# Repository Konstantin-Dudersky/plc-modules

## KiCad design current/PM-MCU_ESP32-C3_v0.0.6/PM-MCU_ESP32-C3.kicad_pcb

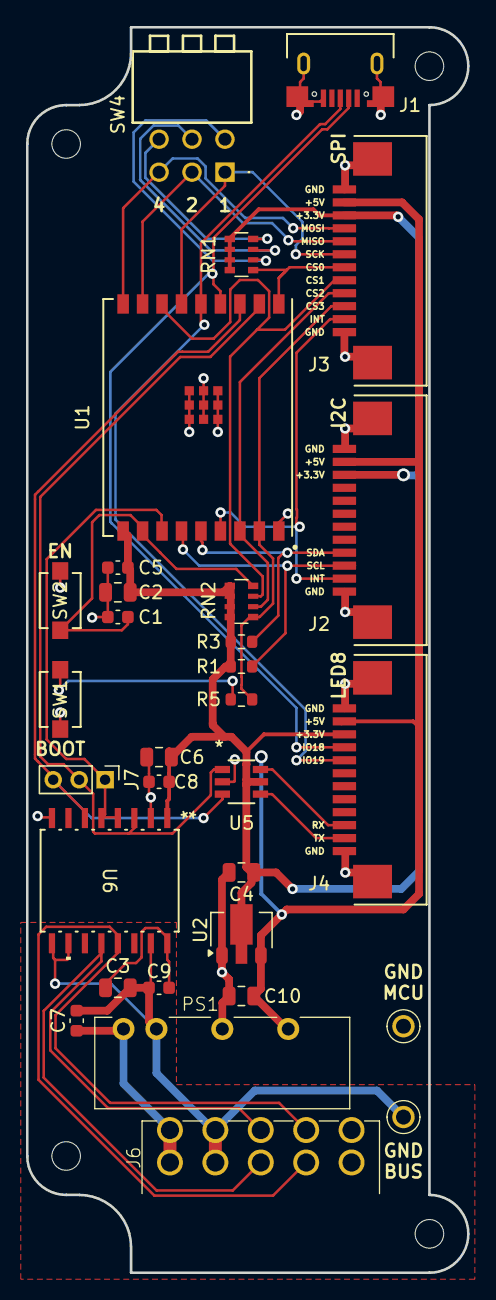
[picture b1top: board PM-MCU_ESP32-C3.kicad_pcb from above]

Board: 2 copper layers, 34.0 x 96.0 mm, 35 parts (0 on the bottom side), 31 nets.

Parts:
C1, C5, C7: 1uF; C_0603_1608Metric
C2, C3, C6, C10: 10uF; C_0805_2012Metric
C4: 22uF; C_0805_2012Metric
C8, C9: 100nF; C_0603_1608Metric
H1, H2, H3, H4: MountingHole_M2
J1: U254-051T-4BH83-S1S; CONN5_H83-S1S_XKB
J2, J3, J4: AFA07-S12FCC-00; CONN10_AFA07-S12_JUS
J6: 15EDGRHC-THR-3.5-10P
J7: PinHeader_01x03_P2.00_THT_straight; PinHeader_1x03_P2.00mm_Vertical
PS1: 24V/5V; B2405LS-1WR3
R1, R3: 3k3; R_0603_1608Metric
R5: 330R; R_0603_1608Metric
RN1, RN2: 10k; R_Array_Convex_4x0603
SW1, SW2: Button; SW_TS-1088_XNP-M
SW4: DIP 3 pos; DA03BLP
U1: ESP32-C3-WROOM-02U-N4; ESP32-C3-WROOM-02U_EXP
U2: CJA1117B-3.3; SOT-89-3
U3, U4: 5117
U5: SN74LVC2G14DBVR; DBV6-M
U6: CA-IS3098W; SOIC16-WBW_CLG

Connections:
+3.3V_BUS: C3.1, C9.1, U6.16 (VISO)
+3.3V_MCU: C2.1, C4.1, C5.1, C6.1, C8.1, J2.10, J3.10, J4.10, R1.1, R3.1, RN1.1 (R1.1), RN1.2 (R2.1), RN1.3 (R3.1), RN1.4 (R4.1), RN2.1 (R1.1), RN2.2 (R2.1), RN2.3 (R3.1), RN2.4 (R4.1), U1.1 (3V3), U2.2 (OUTPUT), U5.5 (VCC), U6.1 (VDD)
+5V_MCU: C10.1, J2.11, J3.11, J4.11, PS1.6 (+V), U2.3 (INPUT)
+24V_BUS: C7.1, J6.1, J6.6 (Pin_2), PS1.1 (Vin)
/A: J6.3, J6.8 (Pin_6), U6.12 (A)
/B: J6.4, J6.9 (Pin_8), U6.13 (B)
/CS0: J3.6, RN1.5 (R4.2), U1.10 (IO10)
/CS1: J3.5, RN2.7 (R2.2), U1.16 (IO2)
/CS2: J3.4, RN2.6 (R3.2), U1.7 (IO8)
/CS3: J3.3, R5.2, RN2.5 (R4.2), U1.8 (IO9)
/EN: C1.1, RN2.8 (R1.2), SW2.2, U1.2 (EN)
/INT: J2.2, J3.2, U1.6 (IO7)
/MISO: J3.8, SW4.2, U1.17 (IO1)
/MOSI: J3.9, SW4.3, U1.18 (IO0)
/SCK: J3.7, SW4.1, U1.15 (IO3)
/SCL: J2.3, R1.2, U1.4 (IO5)
/SDA: J2.4, R3.2, U1.5 (IO6)
/UART_RTS: J7.1, U1.3 (IO4), U6.4 (RE), U6.5 (DE)
/UART_RX: J7.2, U1.11 (RXD_(IO20)), U5.1 (1A), U6.3 (RO)
/UART_TX: J7.3, U1.12 (TXD_(IO21)), U5.3 (2A), U6.6 (DI)
/USB_D+: J1.3 (D+), J4.8, U1.14 (IO19_(USB_D+))
/USB_D-: J1.2 (D-), J4.9, U1.13 (IO18_(USB_D-))
GND_BUS: C3.2, C7.2, C9.2, J6.2 (Pin_3), J6.7 (Pin_4), PS1.2 (GND), U4.1, U6.9 (GNDB), U6.10 (SEL), U6.15 (GNDB)
GND_MCU: C1.2, C2.2, C4.2, C5.2, C6.2, C8.2, C10.2, J1.5 (GND), J2.1, J2.12 (Pin_11), J2.13 (Pin_11), J3.1, J3.12 (Pin_11), J3.13 (Pin_11), J4.1, J4.12 (Pin_11), J4.13 (Pin_11), PS1.4 (0V), SW1.1, SW2.1, U1.9 (GND), U1.EPAD, U2.1 (GND), U3.1, U5.2 (GND), U6.2 (GNDA), U6.8 (GNDA)
unnamed: J4.2, U5.4 (2Y)
unnamed: J4.3, U5.6 (1Y)
unnamed: R5.1, SW1.2
unnamed: RN1.8 (R1.2), SW4.4
unnamed: RN1.7 (R2.2), SW4.5
unnamed: RN1.6 (R3.2), SW4.6
PE: J6.5 (Pin_9), J6.10

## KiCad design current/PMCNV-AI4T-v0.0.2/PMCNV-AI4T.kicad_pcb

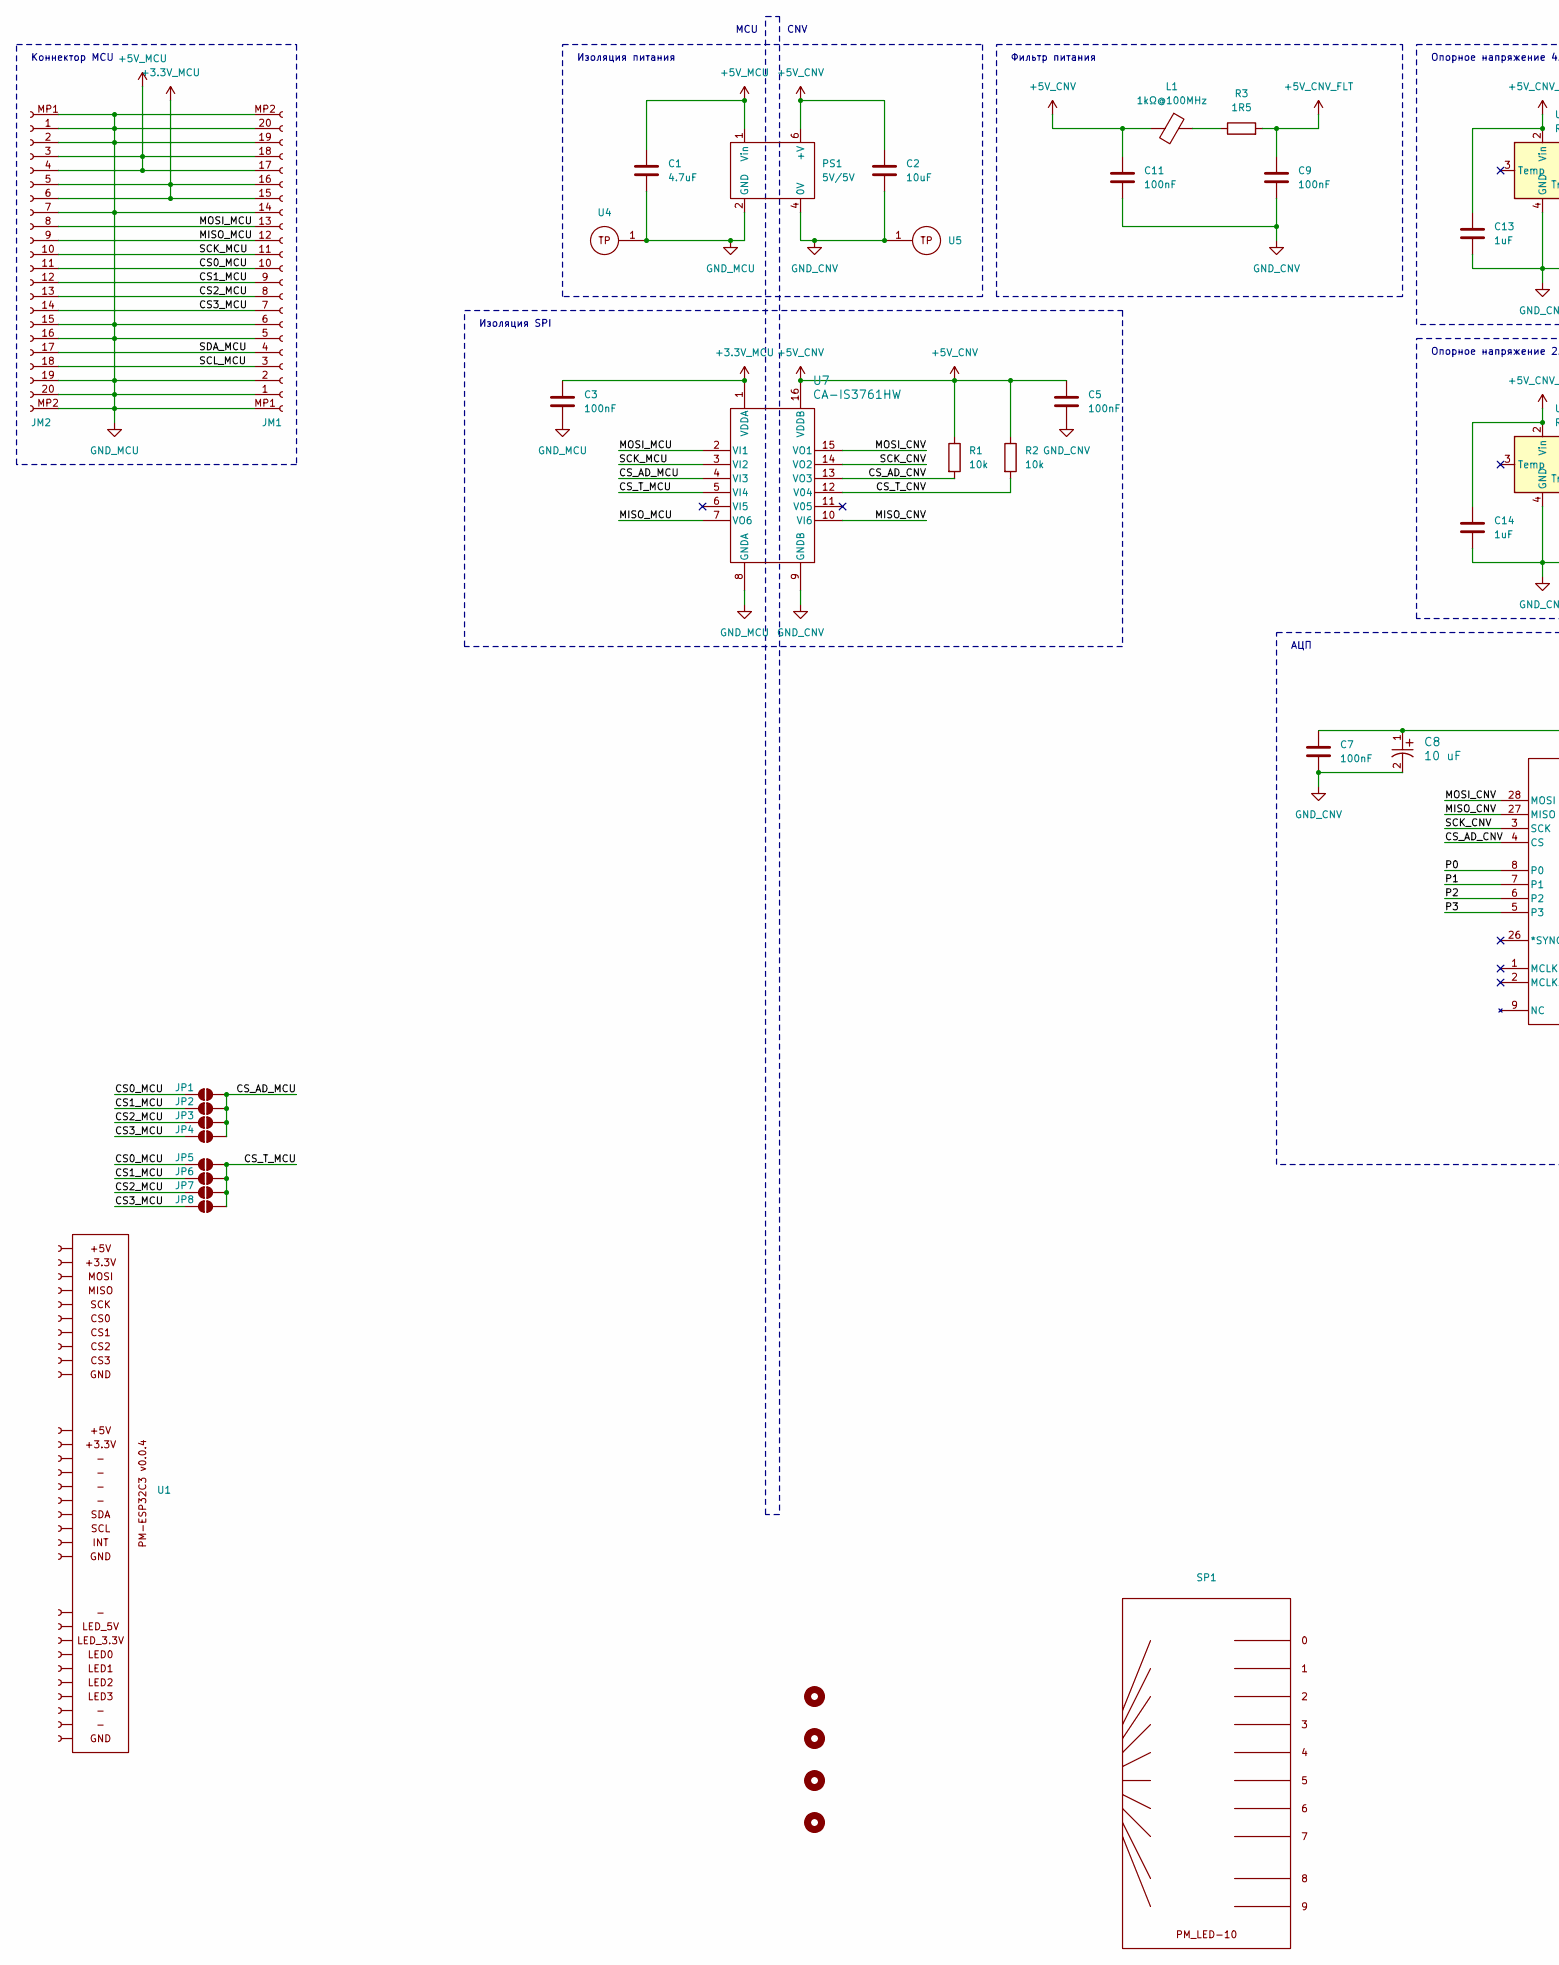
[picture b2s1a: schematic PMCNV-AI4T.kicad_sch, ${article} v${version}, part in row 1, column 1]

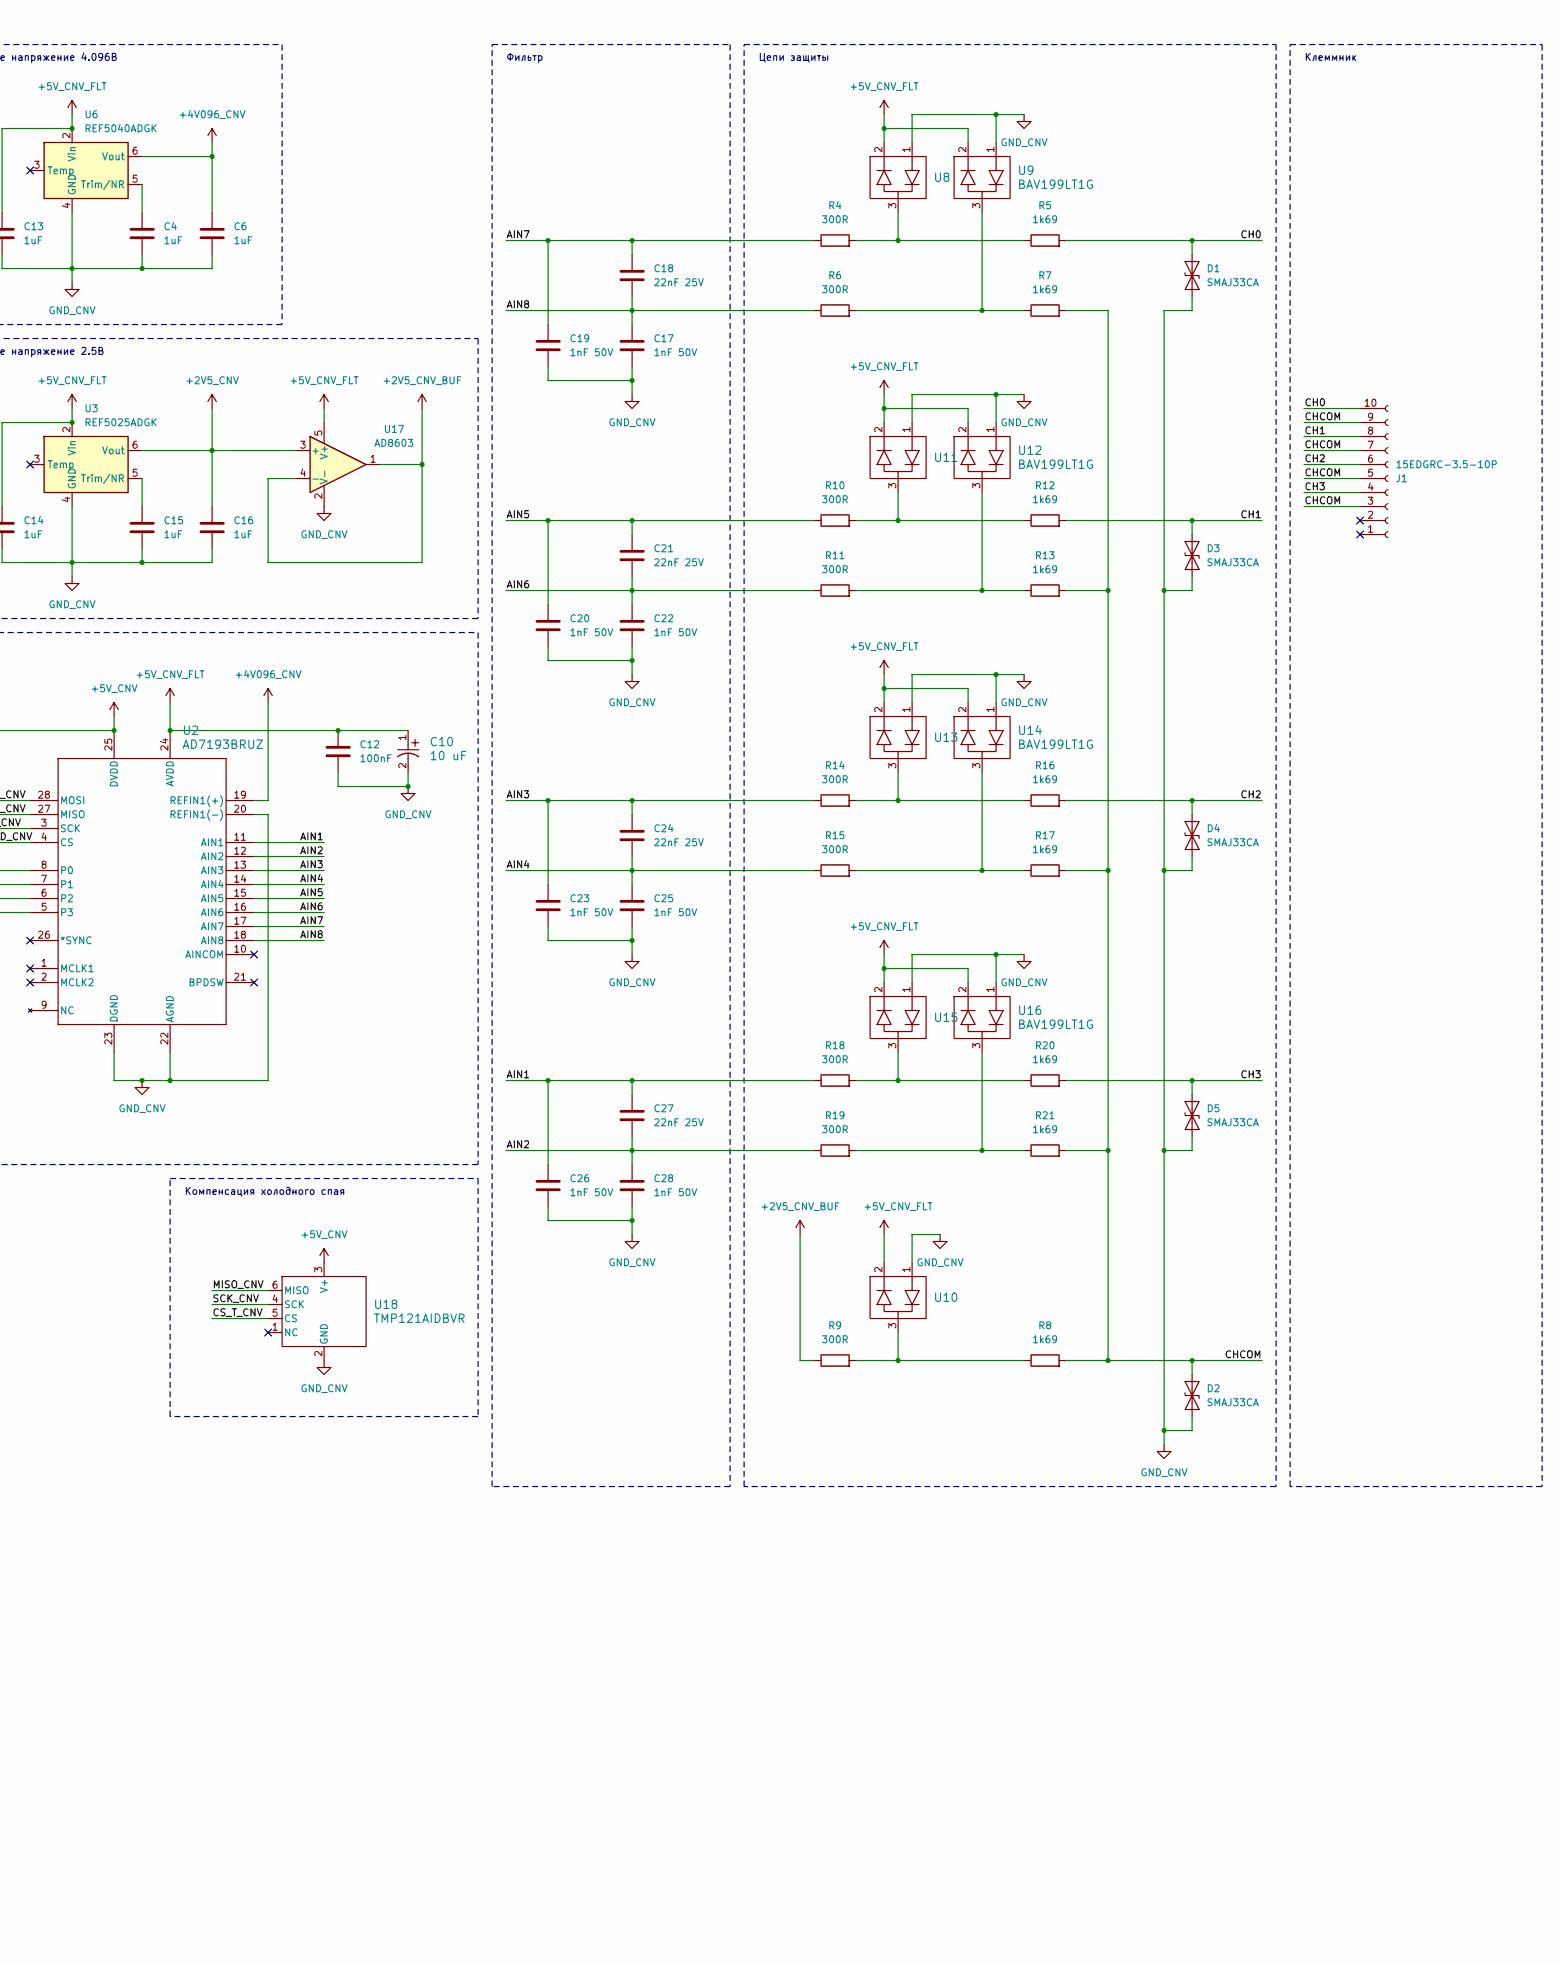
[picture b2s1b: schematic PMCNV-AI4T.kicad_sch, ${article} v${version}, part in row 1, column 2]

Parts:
C1: 4.7uF; C_0805_2012Metric; part_ipn C_4.7uF_16V_0805_MLCC-X7R
C2: 10uF; C_0805_2012Metric; part_ipn C_10uF_16V_0805_MLCC-X7R
C3, C5, C7, C9, C11, C12: 100nF; C_0603_1608Metric; part_ipn C_100nF_16V_0603_MLCC-X7R
C4, C6, C13, C14, C15, C16: 1uF; C_0603_1608Metric; part_ipn C_1uF_16V_0603_MLCC-X7R
C8, C10: 10 uF; TAJA_AVX-M; part_ipn TAJA106M016RNJ
C17, C19, C20, C22, C23, C25, C26, C28: 1nF 50V; C_0603_1608Metric; part_ipn C_1nF_50V_0603_MLCC-X7R
C18, C21, C24, C27: 22nF 25V; C_0603_1608Metric; part_ipn C_22nF_25V_0603_MLCC-X7R
D1, D2, D3, D4, D5: SMAJ33CA; SMASeries_LTF-M; part_ipn SMAJ33CA
H4, H5, H6, H7: MountingHole_M3
J1: 15EDGRC-3.5-10P; part_ipn 15EDGRC-3.5-10P
JM1, JM2: AFA07-S20FCC-00; AFA07S20FCA00; part_ipn AFA07-S20FCC-00
JP1, JP2, JP3, JP4, JP5, JP6, JP7, JP8: SolderJumper_2_Open; SolderJumper-2_P1.3mm_Open_RoundedPad1.0x1.5mm
L1: 1kΩ@100MHz; L_1206_3216Metric_Pad1.42x1.75mm_HandSolder; part_ipn FB_300mΩ_1kΩ@100MHz_1206
PS1: 5V/5V; B2405LS-1WR3; part_ipn B0505LS-1W
R1, R2: 10k; R_0603_1608Metric; part_ipn R_10k_0603_1%
R3: 1R5; R_0603_1608Metric; part_ipn R_1R5_0603_1%
R4, R6, R9, R10, R11, R14, R15, R18, R19: 300R; R_0603_1608Metric; part_ipn R_300R_0603_1%
R5, R7, R8, R12, R13, R16, R17, R20, R21: 1k69; R_0603_1608Metric; part_ipn R_1k69_0603_1%
SP1: PM_LED-xx-v0.0.1; part_ipn PM_LED-10-v0.0.1
U1: PM-ESP32C3_v0.0.5; part_ipn PM-ESP32C3_v0.0.4
U2: AD7193BRUZ; RU_28_ADI; part_ipn AD7193BRUZ
U3: REF5025ADGK; MSOP-8_3x3mm_P0.65mm
U4, U5: 5117; part_ipn Keystone_5117
U6: REF5040ADGK; MSOP-8_3x3mm_P0.65mm
U7: CA-IS3761HW; SOIC16-WBW_CLG-M; part_ipn CA-IS3761HW
U8, U9, U10, U11, U12, U13, U14, U15, U16: BAV199LT1G; SOT-23_ONS
U17: AD8603; TSOT-23-5
U18: TMP121AIDBVR; DBV6

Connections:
+2V5_CNV: C16.1, U3.6 (Vout), U17.3 (+)
+2V5_CNV_BUF: R9.1, U17.1, U17.4 (-)
+3.3V_MCU: C3.1, JM1.15 (Pin_11), JM1.16 (Pin_11), JM2.5, JM2.6, U7.1 (VDDA)
+4V096_CNV: C6.1, U2.19 (REFIN1(+)), U6.6 (Vout)
+5V_CNV: C2.1, C5.2, C7.1, C8.1, C11.1, L1.2, PS1.6 (+V), R1.1, R2.1, U2.25 (DVDD), U7.16 (VDDB), U18.3 (V+)
+5V_CNV_FLT: C9.1, C10.1, C12.1, C13.1, C14.1, R3.2, U2.24 (AVDD), U3.2 (Vin), U6.2 (Vin), U8.2, U9.2, U10.2, U11.2, U12.2, U13.2, U14.2, U15.2, U16.2, U17.5 (V+)
+5V_MCU: C1.1, JM1.17 (Pin_11), JM1.18 (Pin_11), JM2.3, JM2.4, PS1.1 (Vin)
/AIN1: C26.1, C27.1, R18.1, U2.11 (AIN1)
/AIN2: C27.2, C28.1, R19.1, U2.12 (AIN2)
/AIN3: C23.1, C24.1, R14.1, U2.13 (AIN3)
/AIN4: C24.2, C25.1, R15.1, U2.14 (AIN4)
/AIN5: C20.1, C21.1, R10.1, U2.15 (AIN5)
/AIN6: C21.2, C22.1, R11.1, U2.16 (AIN6)
/AIN7: C18.1, C19.1, R4.1, U2.17 (AIN7)
/AIN8: C17.1, C18.2, R6.1, U2.18 (AIN8)
/CH0: D1.2 (A2), J1.10, R5.2
/CH1: D3.2 (A2), J1.8, R12.2
/CH2: D4.2 (A2), J1.6, R16.2
/CH3: D5.2 (A2), J1.4, R20.2
/CHCOM: D2.2 (A2), J1.3, J1.5, J1.7, J1.9, R7.2, R8.2, R13.2, R17.2, R21.2
/CS0_MCU: JM1.10, JM2.11, JP1.1 (A), JP5.1 (A)
/CS1_MCU: JM1.9, JM2.12 (Pin_11), JP2.1 (A), JP6.1 (A)
/CS2_MCU: JM1.8, JM2.13 (Pin_11), JP3.1 (A), JP7.1 (A)
/CS3_MCU: JM1.7, JM2.14 (Pin_11), JP4.1 (A), JP8.1 (A)
/CS_AD_CNV: R1.2, U2.4 (CS), U7.13 (VO3)
/CS_AD_MCU: JP1.2 (B), JP2.2 (B), JP3.2 (B), JP4.2 (B), U7.4 (VI3)
/CS_T_CNV: R2.2, U7.12 (V04), U18.5 (CS)
/CS_T_MCU: JP5.2 (B), JP6.2 (B), JP7.2 (B), JP8.2 (B), U7.5 (VI4)
/MISO_CNV: U2.27 (MISO), U7.10 (VI6), U18.6 (MISO)
/MISO_MCU: JM1.12 (Pin_11), JM2.9, U7.7 (VO6)
/MOSI_CNV: U2.28 (MOSI), U7.15 (VO1)
/MOSI_MCU: JM1.13 (Pin_11), JM2.8, U7.2 (VI1)
/P0: U2.8 (P0)
/P1: U2.7 (P1)
/P2: U2.6 (P2)
/P3: U2.5 (P3)
/SCK_CNV: U2.3 (SCK), U7.14 (VO2), U18.4 (SCK)
/SCK_MCU: JM1.11, JM2.10, U7.3 (VI2)
/SCL_MCU: JM1.3, JM2.18 (Pin_11)
/SDA_MCU: JM1.4, JM2.17 (Pin_11)
GND_CNV: C2.2, C4.2, C5.1, C6.2, C7.2, C8.2, C9.2, C10.2, C11.2, C12.2, C13.2, C14.2, C15.2, C16.2, C17.2, C19.2, C20.2, C22.2, C23.2, C25.2, C26.2, C28.2, D1.1 (A1), D2.1 (A1), D3.1 (A1), D4.1 (A1), D5.1 (A1), PS1.4 (0V), U2.20 (REFIN1(-)), U2.22 (AGND), U2.23 (DGND), U3.4 (GND), U5.1, U6.4 (GND), U7.9 (GNDB), U8.1, U9.1, U10.1, U11.1, U12.1, U13.1, U14.1, U15.1, U16.1, U17.2 (V-), U18.2 (GND)
GND_MCU: C1.2, C3.2, JM1.1, JM1.2, JM1.5, JM1.6, JM1.14 (Pin_11), JM1.19 (Pin_11), JM1.20 (Pin_11), JM1.MP1 (Pin_11), JM1.MP2 (Pin_11), JM2.1, JM2.2, JM2.7, JM2.15 (Pin_11), JM2.16 (Pin_11), JM2.19 (Pin_11), JM2.20 (Pin_11), JM2.MP1 (Pin_11), JM2.MP2 (Pin_11), PS1.2 (GND), U4.1, U7.8 (GNDA)
unnamed: L1.1, R3.1
unnamed: R4.2, R5.1, U8.3
unnamed: R6.2, R7.1, U9.3
unnamed: R8.1, R9.2, U10.3
unnamed: R10.2, R12.1, U11.3
unnamed: R11.2, R13.1, U12.3
unnamed: R14.2, R16.1, U13.3
unnamed: R15.2, R17.1, U14.3
unnamed: R18.2, R20.1, U15.3
unnamed: R19.2, R21.1, U16.3
unnamed: C15.1, U3.5 (Trim/NR)
unnamed: C4.1, U6.5 (Trim/NR)

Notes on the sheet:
Опорное напряжение 2.5В
Опорное напряжение 4.096В
MCU
Изоляция питания
Изоляция SPI
Коннектор MCU
CNV
Фильтр питания
АЦП
Фильтр
Компенсация холодного спая
Цепи защиты
Клеммник

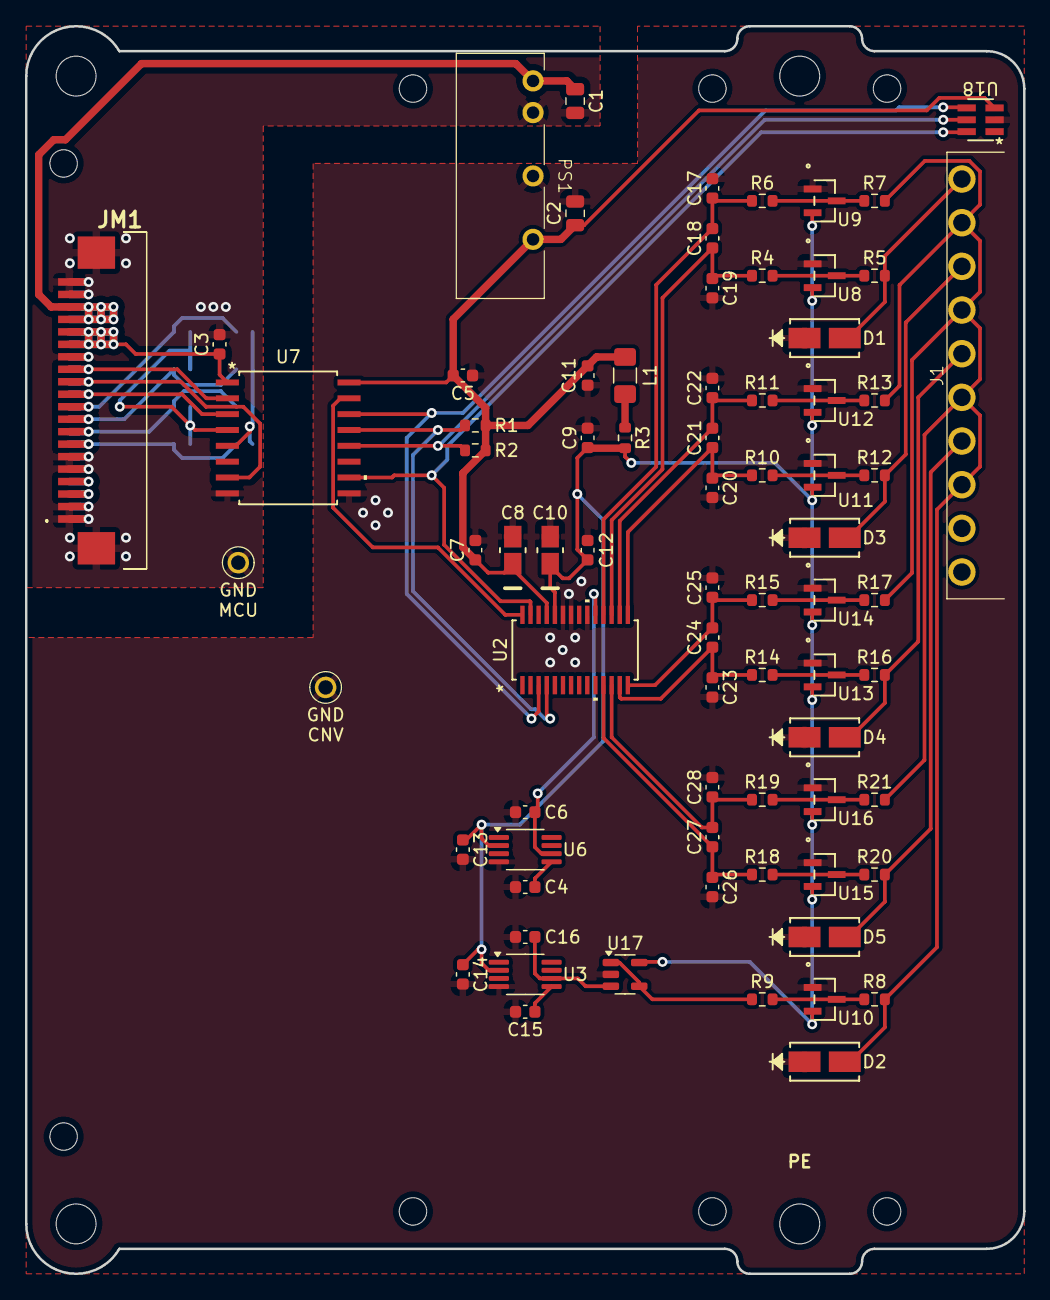
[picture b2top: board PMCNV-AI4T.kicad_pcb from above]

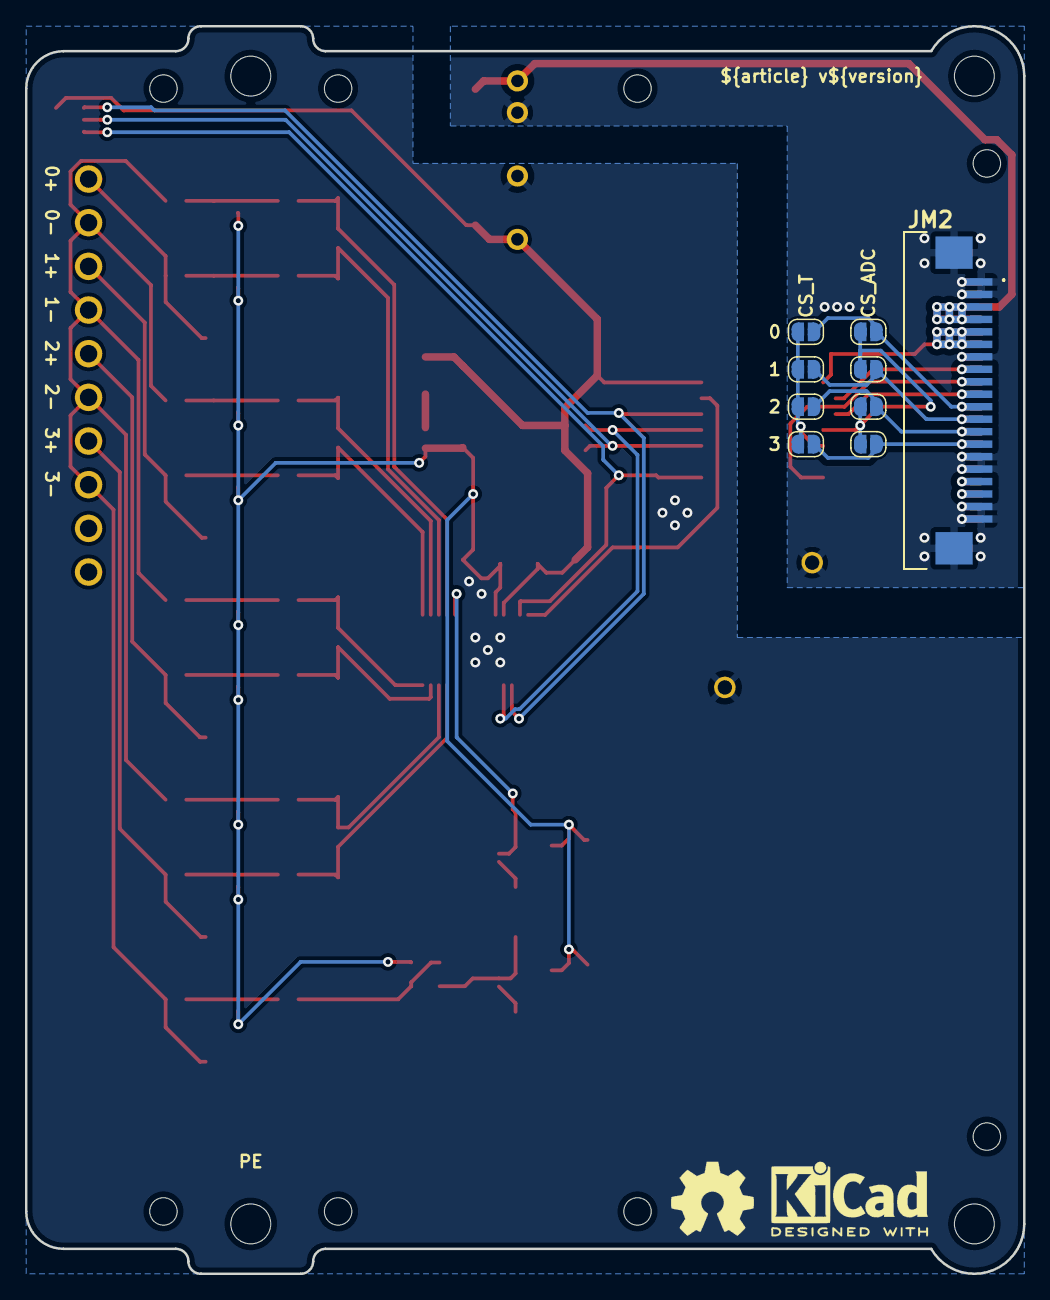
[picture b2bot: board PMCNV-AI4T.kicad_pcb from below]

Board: 2 copper layers, 80.0 x 100.0 mm, 92 parts (11 on the bottom side), 50 nets.

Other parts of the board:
kicad_logo: KiCad-Logo2_5mm_SilkScreen
oshw_logo: OSHW-Symbol_6.7x6mm_SilkScreen

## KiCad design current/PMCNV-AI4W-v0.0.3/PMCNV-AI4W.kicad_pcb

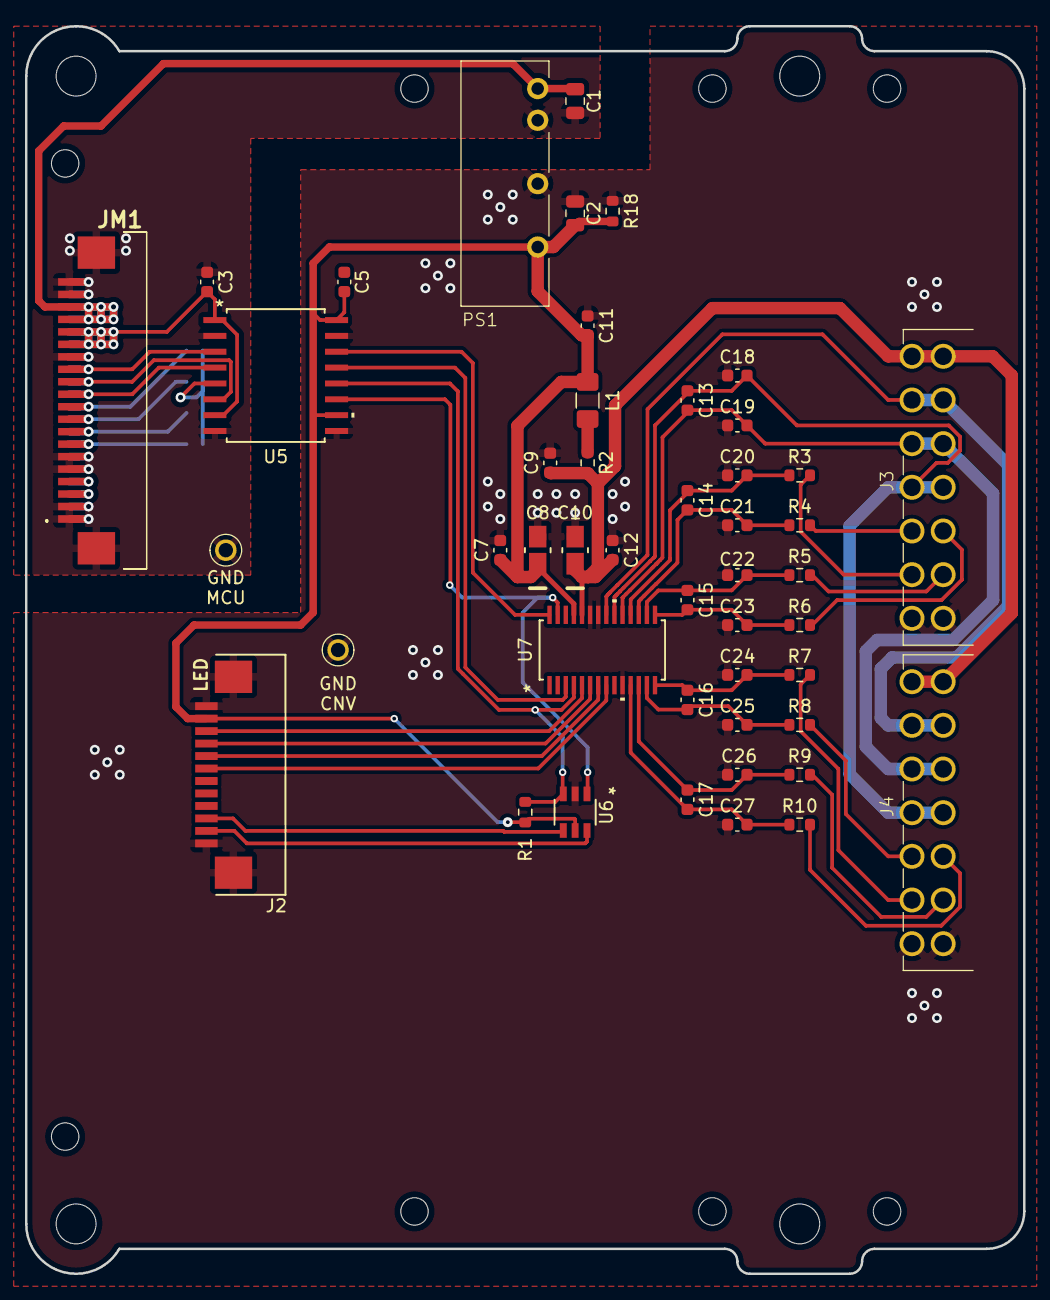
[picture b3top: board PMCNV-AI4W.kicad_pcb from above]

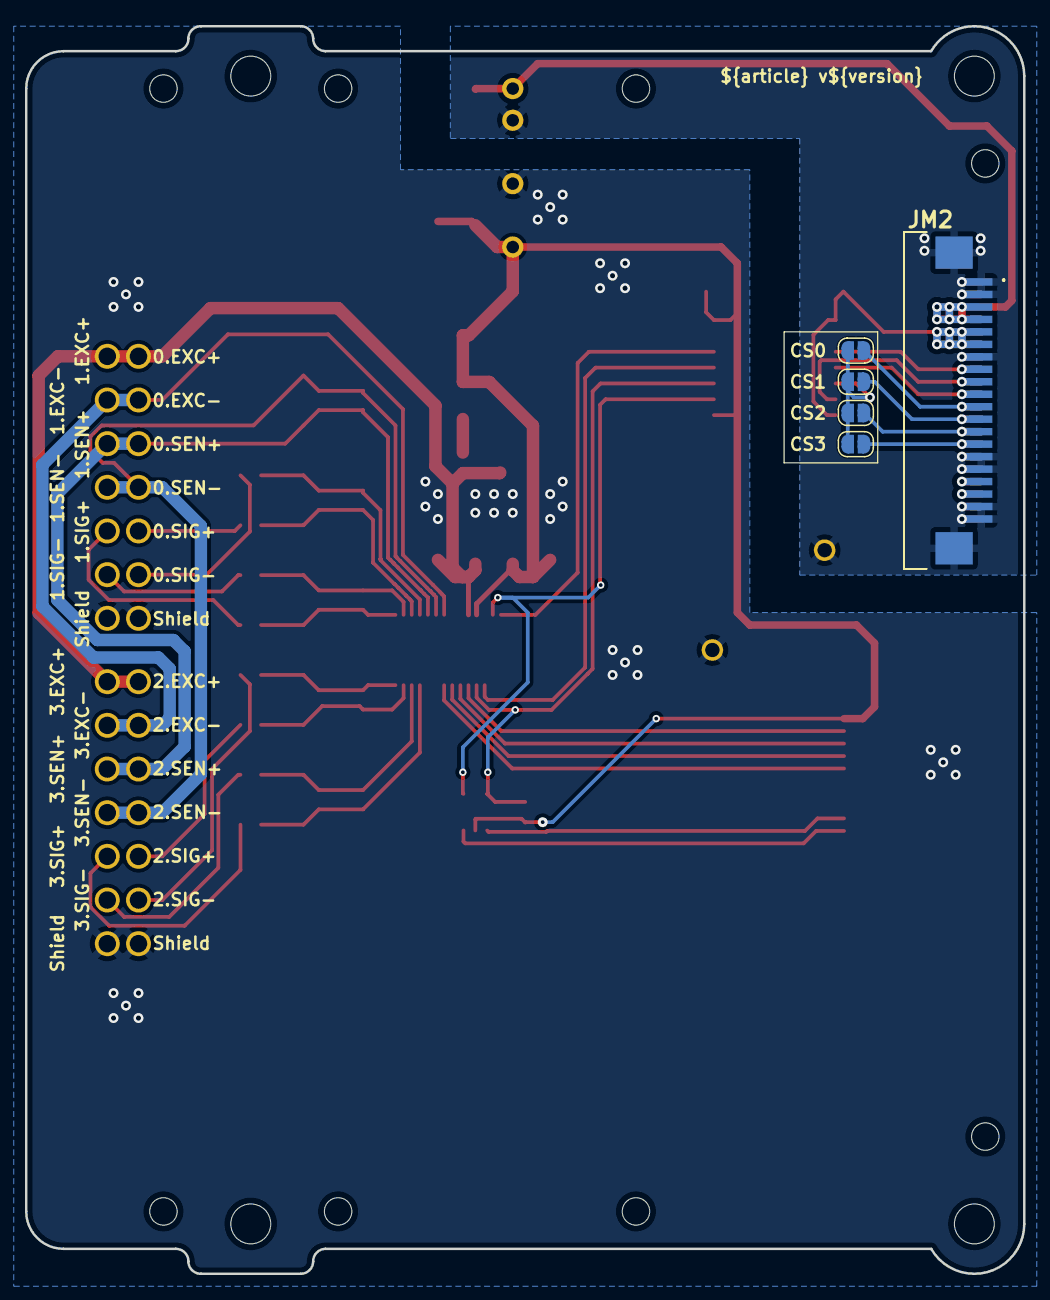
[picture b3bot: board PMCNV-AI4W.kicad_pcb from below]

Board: 2 copper layers, 80.0 x 100.0 mm, 58 parts (5 on the bottom side), 46 nets.

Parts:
C1: 4.7uF; C_0805_2012Metric
C2: 10uF; C_0805_2012Metric
C3, C5, C7, C9, C11, C12: 100nF; C_0603_1608Metric
C8, C10: 10 uF; TAJA_AVX-M
C13: 1uF; C_0603_1608Metric
C14, C15, C16, C17, C18, C19: 10nF; C_0603_1608Metric
C20, C21, C22, C23, C24, C25, C26, C27: 1nF; C_0603_1608Metric
H1, H2, H3, H4: MountingHole_M3
J2: AFA07-S12FCC-00; CONN10_AFA07-S12_JUS
J3, J4: 15EDGRHC-THR-3.5-14P
JM1, JM2: AFA07-S20FCC-00; AFA07S20FCA00
JP1, JP2, JP3, JP4: SolderJumper_2_Open; SolderJumper-2_P1.3mm_Open_RoundedPad1.0x1.5mm
L1: 1kΩ@100MHz; L_1206_3216Metric_Pad1.42x1.75mm_HandSolder
PS1: 5V/5V; B2405LS-1WR3
R1: 10k; R_0603_1608Metric
R2: 1R5; R_0603_1608Metric
R3, R4, R5, R6, R7, R8, R9, R10: 100R; R_0603_1608Metric
R18: 250R; R_0603_1608Metric
SP1: PM_LED-xx-v0.0.1
U1: PM-ESP32C3_v0.0.5
U2, U3: 5117
U5: CA-IS3741HW; SOIC16-WBW_CLG-M
U6: SN74LVC2G14DBVR; DBV6-M
U7: AD7193BRUZ; RU_28_ADI

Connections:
+3.3V_MCU: C3.1, JM1.15 (Pin_11), JM1.16 (Pin_11), JM2.5, JM2.6, U5.1 (VDD), U5.7 (ENA)
+5V_CNV: C2.1, C5.2, C7.1, C8.1, C11.1, J2.11, L1.2, PS1.6 (+V), R1.1, R18.1, U5.10 (ENB), U5.16 (VISO), U6.5 (VCC), U7.25 (DVDD)
+5V_CNV_FLT: C9.1, C10.1, C12.1, J3.7 (Pin_9), J3.14 (Pin_10), J4.7 (Pin_9), J4.14 (Pin_10), R2.2, U7.24 (AVDD)
+5V_MCU: C1.1, JM1.17 (Pin_11), JM1.18 (Pin_11), JM2.3, JM2.4, PS1.1 (Vin)
/0.SIG+: J3.3, R4.2
/0.SIG-: J3.2 (Pin_3), R3.2
/1.SIG+: J3.10 (Pin_6), R6.2
/1.SIG-: J3.9 (Pin_4), R5.2
/2.SIG+: J4.3, R8.2
/2.SIG-: J4.2 (Pin_3), R7.2
/3.SIG+: J4.10 (Pin_6), R10.2
/3.SIG-: J4.9 (Pin_4), R9.2
/AIN1: C17.1, C27.1, R10.1, U7.11 (AIN1)
/AIN2: C17.2, C26.1, R9.1, U7.12 (AIN2)
/AIN3: C16.1, C25.1, R8.1, U7.13 (AIN3)
/AIN4: C16.2, C24.1, R7.1, U7.14 (AIN4)
/AIN5: C15.1, C23.1, R6.1, U7.15 (AIN5)
/AIN6: C15.2, C22.1, R5.1, U7.16 (AIN6)
/AIN7: C14.1, C21.1, R4.1, U7.17 (AIN7)
/AIN8: C14.2, C20.1, R3.1, U7.18 (AIN8)
/CS0_MCU: JM1.10, JM2.11, JP1.1 (A)
/CS1_MCU: JM1.9, JM2.12 (Pin_11), JP2.1 (A)
/CS2_MCU: JM1.8, JM2.13 (Pin_11), JP3.1 (A)
/CS3_MCU: JM1.7, JM2.14 (Pin_11), JP4.1 (A)
/CS_CNV: R1.2, U5.12 (VO3), U6.3 (2A), U7.4 (CS)
/CS_LED: J2.3, U6.4 (2Y)
/CS_MCU: JP1.2 (B), JP2.2 (B), JP3.2 (B), JP4.2 (B), U5.5 (VI3)
/EXC-: J3.6 (Pin_9), J3.13 (Pin_10), J4.6 (Pin_9), J4.13 (Pin_10), U7.21 (BPDSW)
/MISO_CNV: U5.11 (VI4), U6.1 (1A), U7.27 (MISO)
/MISO_LED: J2.2, U6.6 (1Y)
/MISO_MCU: JM1.12 (Pin_11), JM2.9, U5.6 (VO4)
/MOSI_CNV: U5.14 (VO1), U7.28 (MOSI)
/MOSI_MCU: JM1.13 (Pin_11), JM2.8, U5.3 (VI1)
/P0: J2.7, U7.8 (P0)
/P1: J2.8, U7.7 (P1)
/P2: J2.9, U7.6 (P2)
/P3: J2.10, U7.5 (P3)
/SCK_CNV: U5.13 (VO2), U7.3 (SCK)
/SCK_MCU: JM1.11, JM2.10, U5.4 (VI2)
/SCL_MCU: JM1.3, JM2.18 (Pin_11)
/SDA_MCU: JM1.4, JM2.17 (Pin_11)
/SENSE+: C13.1, C19.1, J3.5 (Pin_9), J3.12 (Pin_10), J4.5 (Pin_9), J4.12 (Pin_10), U7.19 (REFIN1(+))
/SENSE-: C13.2, C18.1, J3.4, J3.11 (Pin_8), J4.4, J4.11 (Pin_8), U7.20 (REFIN1(-))
GND_CNV: C2.2, C7.2, C8.2, C9.2, C10.2, C11.2, C12.2, C18.2, C19.2, C20.2, C21.2, C22.2, C23.2, C24.2, C25.2, C26.2, C27.2, J2.1, J2.12 (Pin_11), J2.13 (Pin_11), J3.1, J3.8 (Pin_2), J4.1, J4.8 (Pin_2), PS1.4 (0V), R18.2, U3.1, U5.9 (GNDB), U5.15 (GNDB), U6.2 (GND), U7.10 (AINCOM), U7.22 (AGND), U7.23 (DGND)
GND_MCU: C1.2, C3.2, JM1.1, JM1.2, JM1.5, JM1.6, JM1.14 (Pin_11), JM1.19 (Pin_11), JM1.20 (Pin_11), JM1.MP1 (Pin_11), JM1.MP2 (Pin_11), JM2.1, JM2.2, JM2.7, JM2.15 (Pin_11), JM2.16 (Pin_11), JM2.19 (Pin_11), JM2.20 (Pin_11), JM2.MP1 (Pin_11), JM2.MP2 (Pin_11), PS1.2 (GND), U2.1, U5.2 (GNDA), U5.8 (GNDA)
unnamed: L1.1, R2.1
